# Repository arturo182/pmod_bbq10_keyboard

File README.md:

# BB Q10 Keyboard PMOD

A BB Q10 Keyboard in PMOD format!

This board uses a ATSAMD20 chip as a i2c slave that can be polled to get the key FIFO, the firmware for the SAM can be found here: https://github.com/arturo182/bbq10kbd_i2c_sw

The SAM chip also controls the backlight of the keyboard, the backlight brightness can be controlled over I2C as well.

A kernel module for the Raspberry Pi is available here: https://github.com/arturo182/bbq10pmod_module

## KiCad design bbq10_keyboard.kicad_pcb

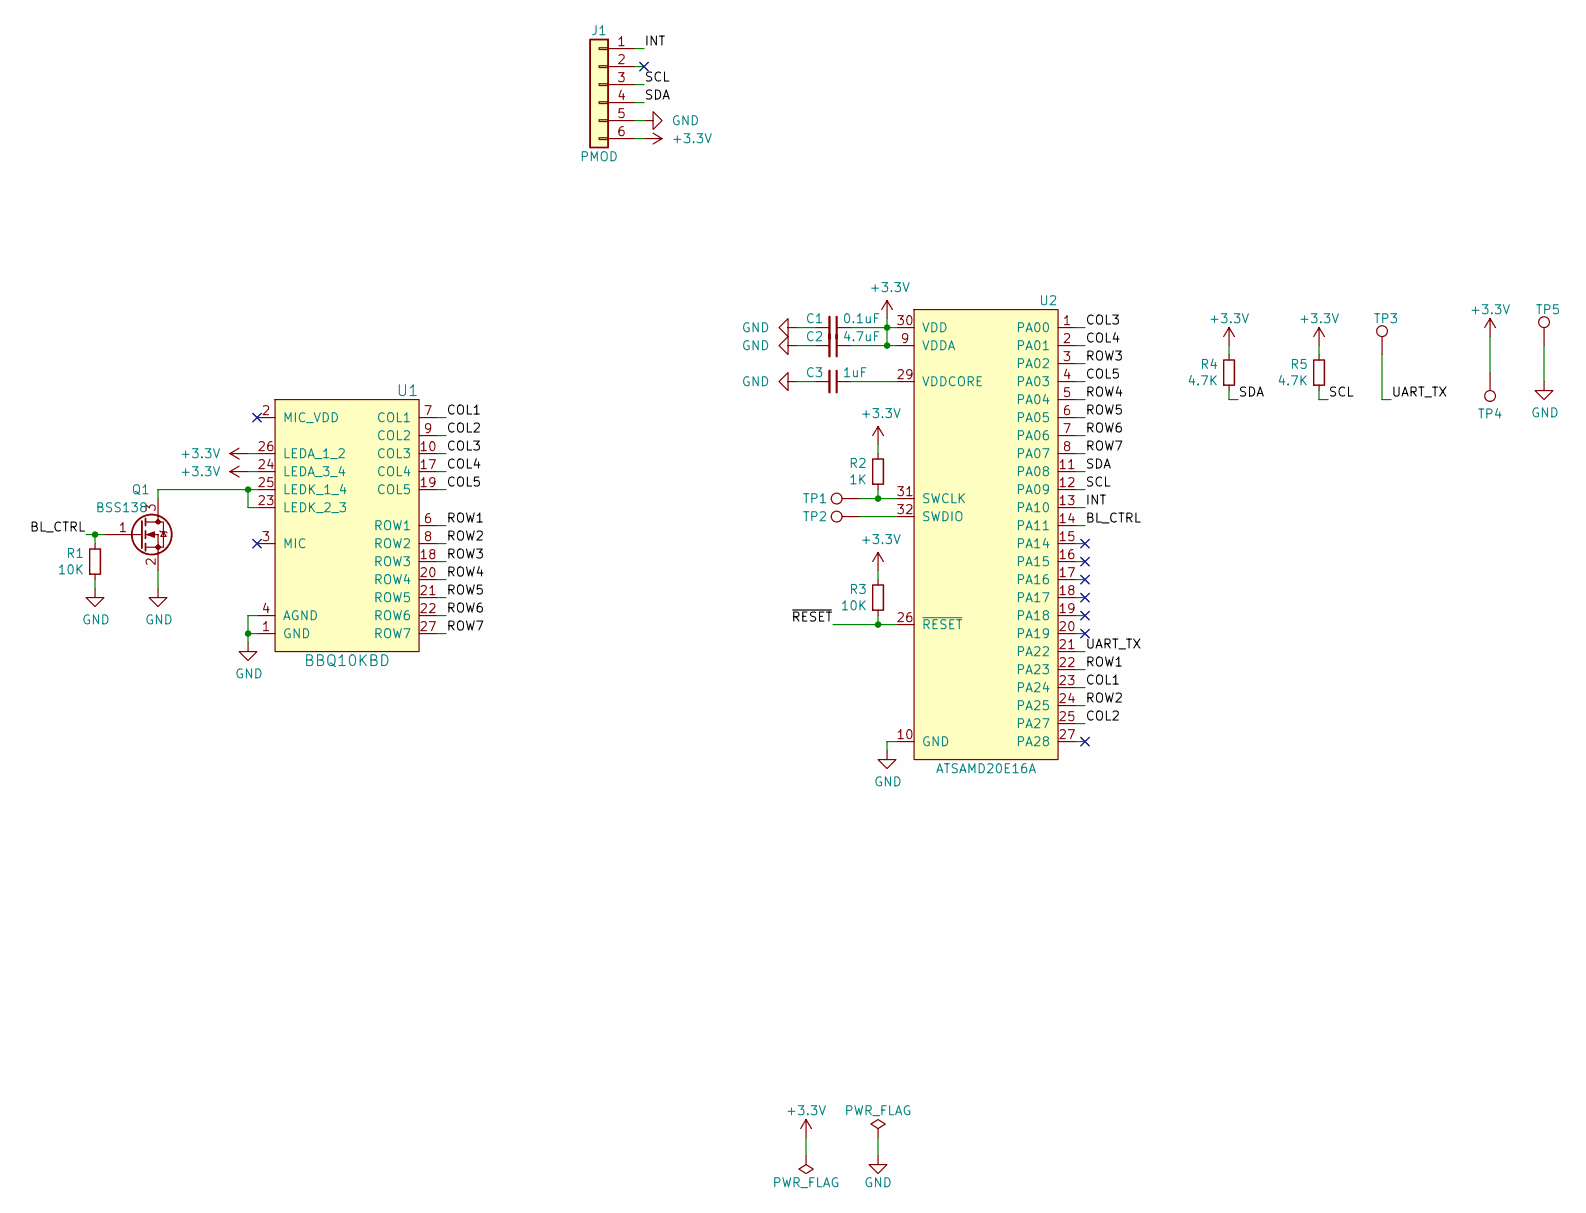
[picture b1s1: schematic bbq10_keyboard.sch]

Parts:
C1: 0.1uF; C_0603_1608Metric
C2: 4.7uF; C_0603_1608Metric
C3: 1uF; C_0603_1608Metric
J1: PMOD; PMODPinHeader_1x06_P2.54mm_Horizontal
Q1: BSS138; SOT-23
R1, R3: 10K; R_0603_1608Metric
R2: 1K; R_0603_1608Metric
R4, R5: 4.7K; R_0603_1608Metric
TP1: TP_SWCLK; TestPoint_Pad_D1.0mm
TP2: TP_SWDIO; TestPoint_Pad_D1.0mm
TP3: UART_TX; TestPoint_Pad_D1.0mm
TP4: VDD; TestPoint_Pad_D1.0mm
TP5: GND; TestPoint_Pad_D1.0mm
U1: BBQ10KBD; BM14B(0.8)-24DS-0.4V(53)
U2: ATSAMD20E16A; QFN-32-1EP_5x5mm_P0.5mm_EP3.45x3.45mm

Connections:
+3V3: C1.1, C2.1, J1.6, R2.2, R3.2, R4.2, R5.2, TP4.1, U1.24 (LEDA_3_4), U1.26 (LEDA_1_2), U2.9 (VDDA), U2.30 (VDD)
/BL_CTRL: Q1.1 (G), R1.2, U2.14 (PA11)
/COL1: U1.7 (COL1), U2.23 (PA24)
/COL2: U1.9 (COL2), U2.25 (PA27)
/COL3: U1.10 (COL3), U2.1 (PA00)
/COL4: U1.17 (COL4), U2.2 (PA01)
/COL5: U1.19 (COL5), U2.4 (PA03)
/INT: J1.1, U2.13 (PA10)
/ROW1: U1.6 (ROW1), U2.22 (PA23)
/ROW2: U1.8 (ROW2), U2.24 (PA25)
/ROW3: U1.18 (ROW3), U2.3 (PA02)
/ROW4: U1.20 (ROW4), U2.5 (PA04)
/ROW5: U1.21 (ROW5), U2.6 (PA05)
/ROW6: U1.22 (ROW6), U2.7 (PA06)
/ROW7: U1.27 (ROW7), U2.8 (PA07)
/SCL: J1.3, R5.1, U2.12 (PA09)
/SDA: J1.4, R4.1, U2.11 (PA08)
/UART_TX: TP3.1, U2.21 (PA22)
/~RESET~: R3.1, U2.26 (~RESET~)
GND: C1.2, C2.2, C3.2, J1.5, Q1.2 (S), R1.1, TP5.1, U1.1 (GND), U1.4 (AGND), U1.5 (GND), U1.11 (GND), U1.12 (GND), U1.13 (GND), U1.14 (GND), U1.15 (GND), U1.16 (GND), U1.28 (GND), U2.10 (GND), U2.28 (GND)
unnamed: C3.1, U2.29 (VDDCORE)
unnamed: Q1.3 (D), U1.23 (LEDK_2_3), U1.25 (LEDK_1_4)
unnamed: R2.1, TP1.1, U2.31 (SWCLK)
unnamed: TP2.1, U2.32 (SWDIO)

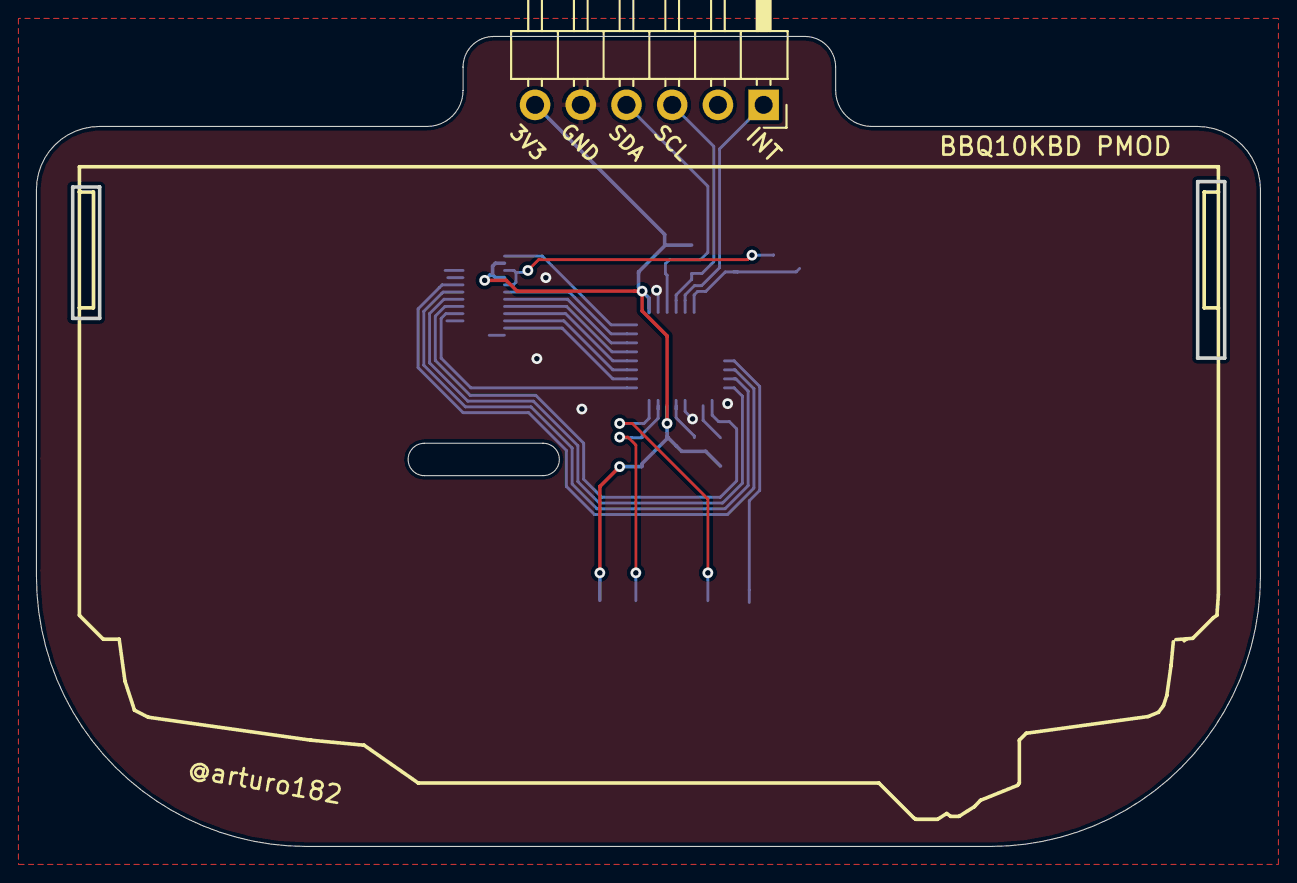
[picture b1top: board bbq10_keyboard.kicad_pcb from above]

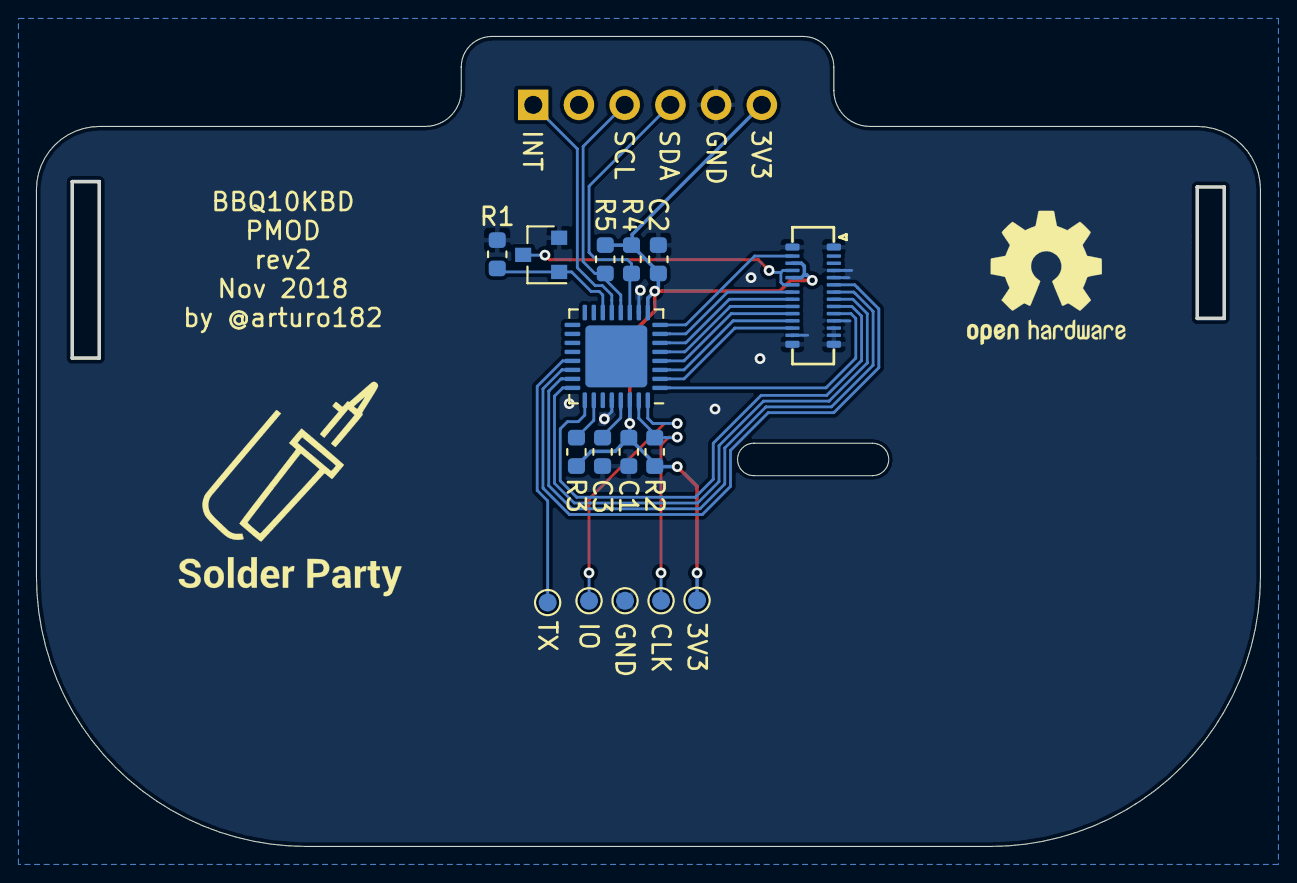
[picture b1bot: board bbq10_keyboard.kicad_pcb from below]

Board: 2 copper layers, 68.0 x 45.0 mm, 17 parts (16 on the bottom side), 24 nets.

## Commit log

2018-11-25 Initial import
2018-11-29 rev2
    - Made the right keyboard hole larger
    - Moved the conenctor to the back
    - Rerouted everything
    - Fixed the damn 0201 footprints
2018-11-29 Add schematic and update bom
2019-05-11 Moved ibom, renamed schematic, added 3D model
2019-05-11 Added README and images
2020-01-03 Create LICENSE
